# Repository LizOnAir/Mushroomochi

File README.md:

# Mushroomochi
Instead of tamagotchi, why not grow your own mushroom? I built this because seeing other people raising their own pets, I wonder what if I raise something different? Something between animal and plants ...... that's how I got the idea of growing a **fungi** :D
Inspired by house of Smurf lol

## Features:
- power with battery
- cuteee
- 3 buttons
- sound and haptic feedback

## CAD Model:

Made in Fusion360.Liz
Access files in [CAD folder](https://github.com/LizOnAir/Mushroomochi/tree/main/CAD).

## PCB
Here's my PCB! It was made in KiCad. 
### Schematic

### PCB

Access files in [PCB folder](https://github.com/LizOnAir/Mushroomochi/tree/main/PCB).

## Firmware
I use Arduino IDE for programming:
- state = eat, sleep, play
- mood = happy, neutral, sad, dead

Access files in [Firmware folder](https://github.com/LizOnAir/Mushroomochi/tree/main/Firmware).

## BOM:
Here should be [everything](https://docs.google.com/spreadsheets/d/1aQkmHvjIL8KsujCnq7xUY5sLrMyQ4HTqEKC24XpwhOs/edit?usp=sharing) you need to make this:
- 1x PCB
- 3x buttons
- 1x vibration motor
- 1x passive buzzer
- 1x 0.96inch OLED
- 1x ESP32-C6
- 2x M3 Brass insert
- 2x M3 screw
- 1x 3.7V Lipo Battery

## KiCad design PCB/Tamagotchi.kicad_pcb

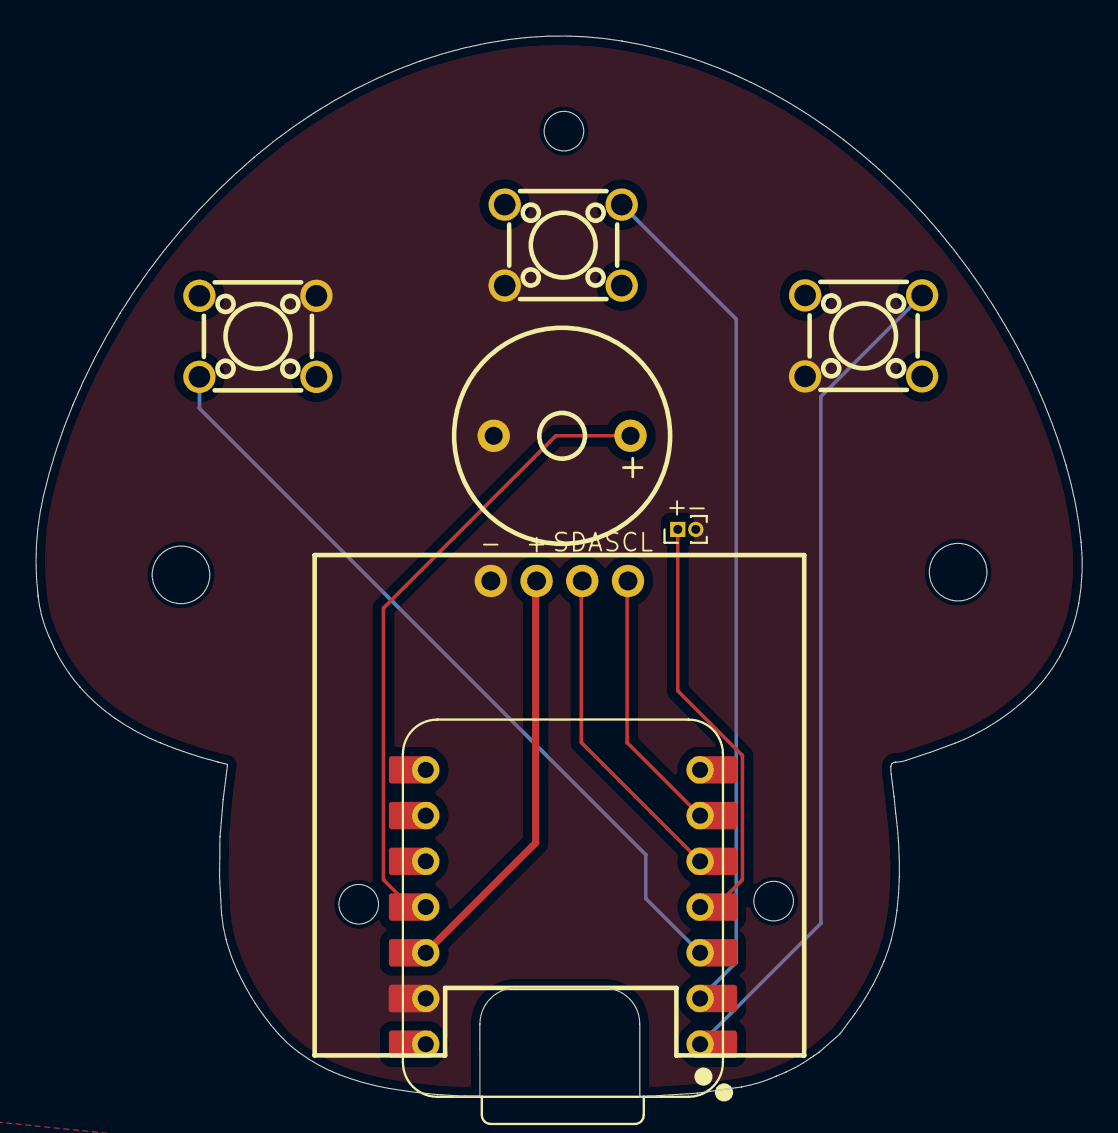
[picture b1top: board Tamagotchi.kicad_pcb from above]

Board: 2 copper layers, 58.1 x 58.9 mm, 7 parts (0 on the bottom side), 9 nets.

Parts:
BUZZER1: TMB12A03; Active_Buzzer
J1: Conn_01x02_Pin; PinHeader_1x02_P1.00mm_Vertical
SW1, SW2, SW3: C13828
U2: HS96L03W2C03; 0_96_OLED
U3: XIAO-ESP32-C6-SMD; XIAO-ESP32C6-DIP

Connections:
+3V3: U2.2 (VCC), U3.12 (3V3)
GND: BUZZER1.2, J1.2, SW1.3, SW2.3, SW3.3, U2.1 (GND), U3.13 (GND)
GPIO0_A0_D0: SW1.2, U3.1 (GPIO0_A0_D0)
GPIO1_A1_D1: SW2.2, U3.2 (GPIO1_A1_D1)
GPIO2_A2_D2: SW3.2, U3.3 (GPIO2_A2_D2)
GPIO18_D10_MOSI: BUZZER1.1 (+), U3.11 (GPIO18_D10_MOSI)
GPIO21_D3: J1.1, U3.4 (GPIO21_D3)
GPIO22_D4_SDA: U2.3 (SCL), U3.5 (GPIO22_D4_SDA)
GPIO23_D5_SCL: U2.4 (SDA), U3.6 (GPIO23_D5_SCL)

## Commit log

2026-04-19 Rename Tamagotchi.kicad_sch to PCB/Tamagotchi.kicad_sch
2026-04-21 Rename Mushroomochi.ino to Firmware/Mushroomochi.ino
2026-04-21 Rename Mushroomochi.step to CAD/Mushroomochi.step
2026-05-01 Enhance README with project motivation and inspiration
    Expanded project description to include personal motivation and inspiration.
